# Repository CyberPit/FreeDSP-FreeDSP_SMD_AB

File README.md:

# FreeDSP-FreeDSP_SMD_AB

- 2in4out RCA jacks
- A/B Selectable Boot EEPROMs
- ADAU1701 Single Board solution
- 0805(2.0mm x 1.25mm) SMD Resistors
- Through-hole Ele-Caps for better Audio performance
- 2V RMS Unity Gain Analog Audio I/O
- Absolute Phase Transparent.
- Power ON/OFF Audio Pops-Muting
- Buffered I2S I/O Headers (with Output Enable control feature)
- Onboard three semi-potentiometers or external controls via header pin. 

Project web page: (Direct Link)
https://cyberpithilo.web.fc2.com/audio/freedsp/index.html

Project web page: (Yandex Machine Translation)
https://translate.yandex.com/translate?url=https%3A%2F%2Fcyberpithilo.web.fc2.com%2Faudio%2Ffreedsp%2Findex.html&lang=ja-en

Project web page: (Google Machine Translation)
https://translate.google.com/translate?hl=ja&sl=ja&tl=en&u=https%3A%2F%2Fcyberpithilo.web.fc2.com%2Faudio%2Ffreedsp%2Findex.html

I registered this design at SeedStudio(FusionPCB) project Gallary, so you can order this board here easily https://www.seeedstudio.com/FreeDSP-SMD-A-B-ADAU1701-1401-Audio-DSP-Processing-Boar-g-1230721

# License
This work and all other materials under https://github.com/freeDSP are licensed under a Creative Commons Attribution Share-Alike 4.0 license. This allows for both personal and commercial derivative works, as long as they credit freeDSP and release their designs under the same license.

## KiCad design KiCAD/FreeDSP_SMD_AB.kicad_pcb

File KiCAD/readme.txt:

This PCB design was inherit from FreeDSP SMD.
Canages and improved in many points.
- Unity Gain I/O
- Selectable boot EEPROM
- Power ON/OFF Mute
- Buffered I2S I/O Headers

Errata: R49 47k ohms --> 4.7k ohms (Need to pull-up strong)

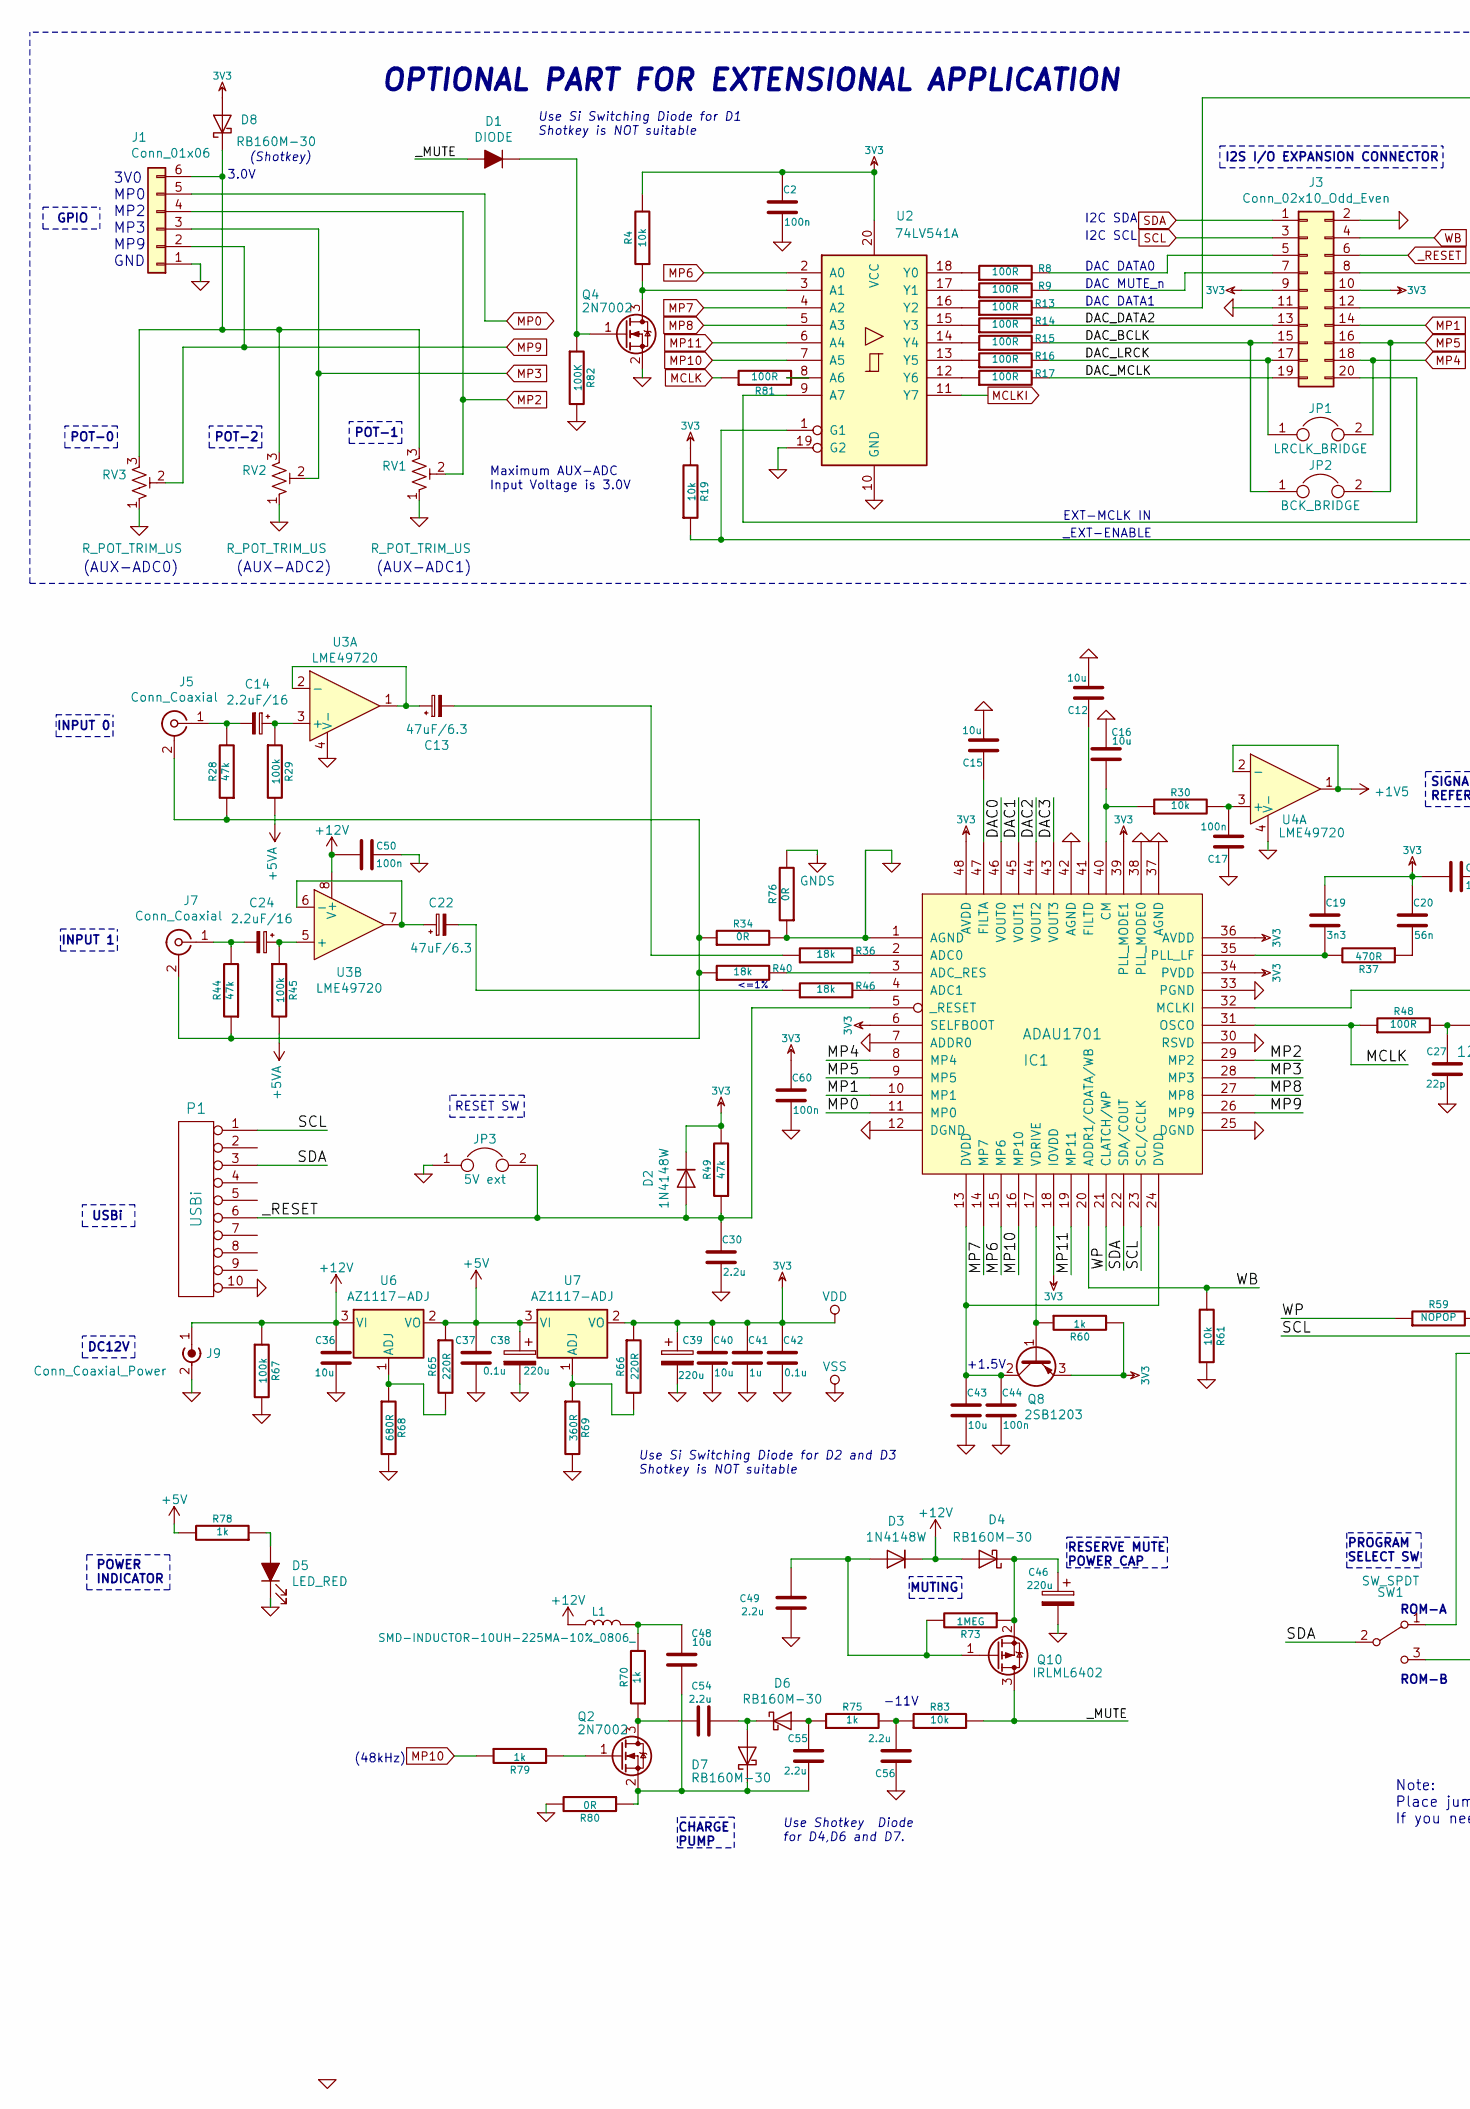
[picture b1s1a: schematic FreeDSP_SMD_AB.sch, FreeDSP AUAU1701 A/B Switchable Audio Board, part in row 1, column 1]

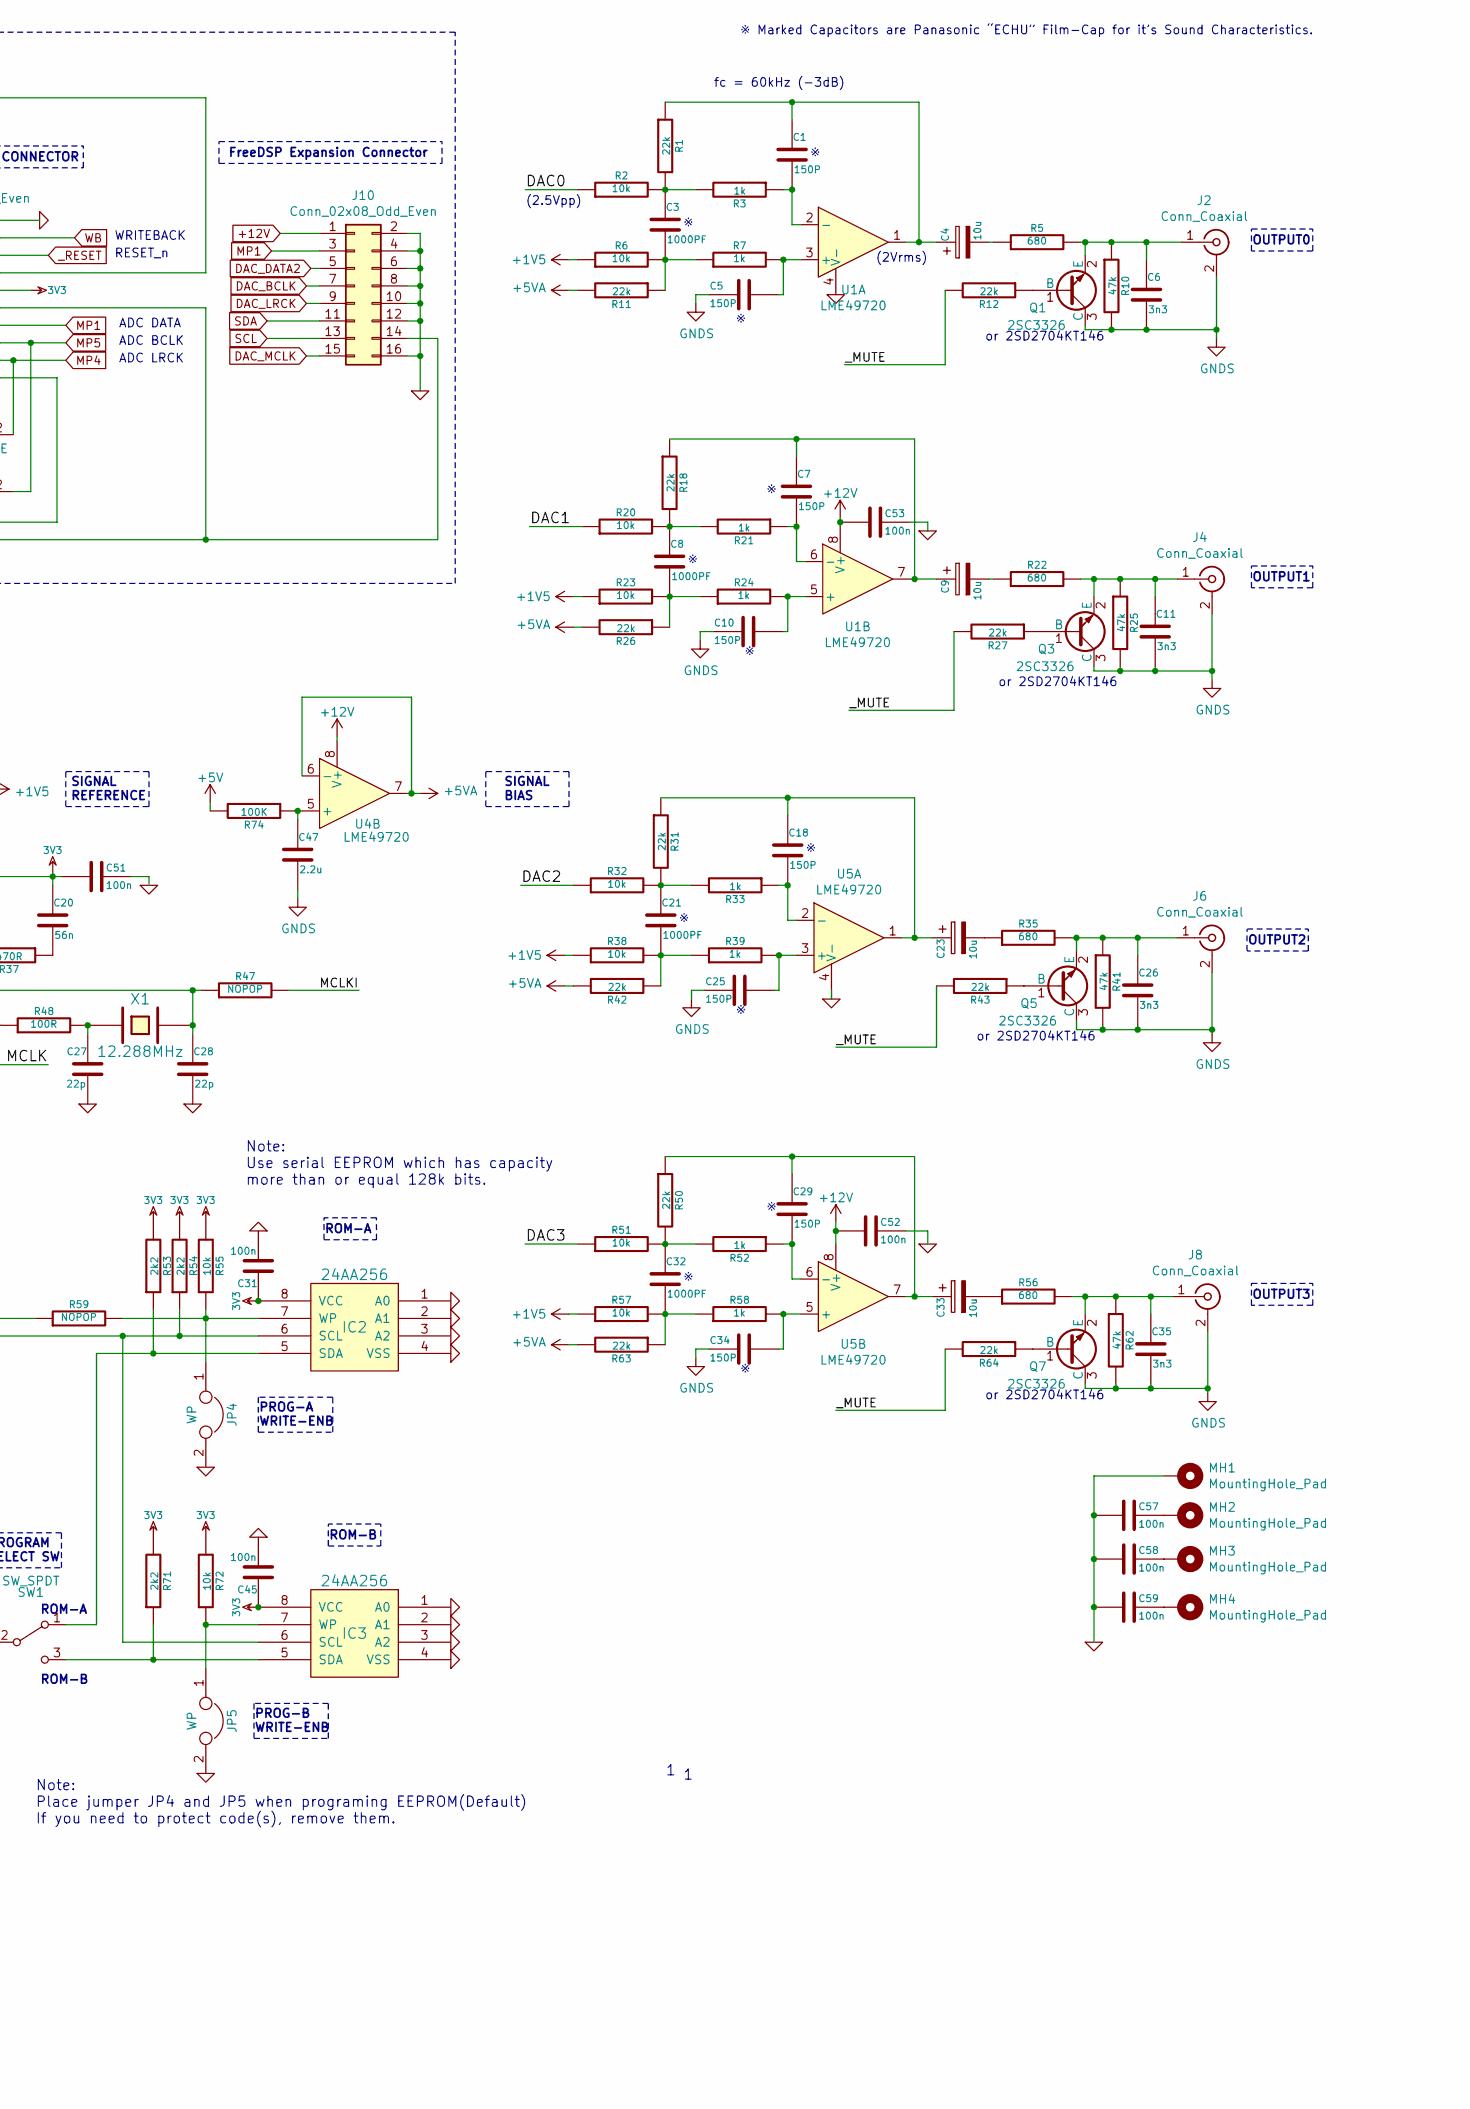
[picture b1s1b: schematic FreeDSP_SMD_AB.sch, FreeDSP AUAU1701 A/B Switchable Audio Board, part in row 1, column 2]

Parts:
C1, C5, C7, C10, C18, C25, C29, C34: 150P; C_0805_HandSoldering
C2, C17, C31, C44, C45, C50, C51, C52, C53, C57, C58, C59, C60: 100n; C_0805_HandSoldering
C3, C8, C21, C32: 1000PF; C_0805_HandSoldering
C4, C9, C23, C33: 10u; CP_Radial_D5.0mm_P2.00mm
C6, C11, C19, C26, C35: 3n3; C_0805_HandSoldering
C12, C15, C16, C36, C40, C43: 10u; C_0805_HandSoldering
C13, C22: 47uF/6.3; CP_Radial_D4.0mm_P2.00mm
C14, C24: 2.2uF/16; CP_Radial_D4.0mm_P2.00mm
C20: 56n; C_0805_HandSoldering
C27, C28: 22p; C_0805_HandSoldering
C30, C47, C49, C54, C55, C56: 2.2u; C_0805_HandSoldering
C37, C42: 0.1u; C_0805_HandSoldering
C38, C39: 220u; CP_Radial_D8.0mm_P5.00mm
C41: 1u; C_0805_HandSoldering
C46: 220u; CP_Radial_Tantal_D10.5mm_P5.00mm
C48: 10u; C_1206_HandSoldering
D1: DIODE; D_SOD-123
D2, D3: 1N4148W; D_SOD-123
D4, D6, D7, D8: RB160M-30; D_SOD-123
D5: LED_RED; LED_0603_HandSoldering
IC1: ADAU1701; LQFP-48_7x7mm_Pitch0.5mm
IC2, IC3: 24AA256; SOIC-8_3.9x4.9mm_Pitch1.27mm
J1: Conn_01x06; TerminalBlock_Phoenix_MPT-2.54mm_6pol
J2, J4, J5, J6, J7, J8: Conn_Coaxial; RJ-2410N
J3: Conn_02x10_Odd_Even; Multicomp_MC9A12-2034_2x10x2.54mm_Straight
J9: Conn_Coaxial_Power; BARREL_JACK
J10: Conn_02x08_Odd_Even; Pin_Header_Straight_2x08_Pitch2.54mm
JP1: LRCLK_BRIDGE; Pin_Header_Straight_1x02_Pitch2.54mm
JP2: BCK_BRIDGE; Pin_Header_Straight_1x02_Pitch2.54mm
JP3: 5V ext; Pin_Header_Straight_1x02_Pitch2.54mm
JP4, JP5: WP; Pin_Header_Straight_1x02_Pitch2.54mm
L1: SMD-INDUCTOR-10UH-225MA-10%_0806_; Inductor_1212; MPN LQH2MCN100K02L
MH1: MountingHole_Pad; MountingHole_3.2mm_M3_Pad_Via
MH2, MH3, MH4: MountingHole_Pad; MountingHole_3.2mm_M3_Pad
P1: USBi; Multicomp_MC9A12-1034_2x05x2.54mm_Straight
Q1, Q3, Q5, Q7: 2SC3326; SOT-23
Q2, Q4: 2N7002; SOT-23
Q8: 2SB1203; TO-252-2
Q10: IRLML6402; SOT-23
R1, R11, R12, R18, R26, R27, R31, R42, R43, R50, R63, R64: 22k; R_0805_HandSoldering
R2, R4, R6, R19, R20, R23, R30, R32, R38, R51, R55, R57, R61, R72, R83: 10k; R_0805_HandSoldering
R3, R7, R21, R24, R33, R39, R52, R58, R60, R70, R75, R78, R79: 1k; R_0805_HandSoldering
R5, R22, R35, R56: 680; R_0805_HandSoldering
R8, R9, R13, R14, R15, R16, R17, R48, R81: 100R; R_0805_HandSoldering
R10, R25, R28, R41, R44, R49, R62: 47k; R_0805_HandSoldering
R29, R45, R67: 100k; R_0805_HandSoldering
R34, R76, R80: 0R; R_0805_HandSoldering
R36, R40, R46: 18k; R_0805_HandSoldering
R37: 470R; R_0805_HandSoldering
R47, R59: NOPOP; R_0805_HandSoldering
R53, R54, R71: 2k2; R_0805_HandSoldering
R65, R66: 220R; R_0805_HandSoldering
R68: 680R; R_0805_HandSoldering
R69: 360R; R_0805_HandSoldering
R73: 1MEG; R_0805_HandSoldering
R74, R82: 100K; R_0805_HandSoldering
RV1, RV2, RV3: R_POT_TRIM_US; Potentiometer_Trimmer_Bourns_3339P_Horizontal
SW1: SW_SPDT; Switch_Slide_11.6x4mm_EG1218
U1, U3, U4, U5: LME49720; SOIC127P600X175-8N
U2: 74LV541A; TSSOP-20_W4.4mm
U6, U7: AZ1117-ADJ; SOT-223-3_TabPin2
X1: 12.288MHz; Crystal_HC49-U_Vertical

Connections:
3V3: C2.1, C19.1, C20.1, C31.1, C39.1, C40.1, C41.1, C42.1, C45.1, C51.2, C60.1, D2.1 (K), D8.2 (A), IC1.6 (SELFBOOT), IC1.18 (IOVDD), IC1.34 (PVDD), IC1.36 (AVDD), IC1.39 (PLL_MODE1), IC1.48 (AVDD), IC2.8 (VCC), IC3.8 (VCC), J3.9, J3.10, Q8.3 (E), R4.2, R19.2, R49.2, R53.2, R54.2, R55.2, R60.2, R66.1, R71.2, R72.2, U2.20 (VCC), U7.2 (VO)
+1V5: R6.1, R23.1, R38.1, R57.1, U4.1, U4.2 (-)
+5V: C37.1, C38.1, R65.1, R74.2, R78.2, U6.2 (VO), U7.3 (VI)
+5VA: R11.2, R26.2, R29.2, R42.2, R45.2, R63.2, U4.6 (-), U4.7
+12V: C36.1, C50.2, C52.2, C53.2, D3.1 (K), D4.2 (A), J9.1 (In), J10.1, L1.1, R67.1, U1.8 (V+), U3.8 (V+), U4.8 (V+), U5.8 (V+), U6.3 (VI)
/DAC0: IC1.46 (VOUT0), R2.1
/DAC1: IC1.45 (VOUT1), R20.1
/DAC2: IC1.44 (VOUT2), R32.1
/DAC3: IC1.43 (VOUT3), R51.1
/WP: IC1.21 (CLATCH/WP), R59.1
/_MUTE: D1.2 (A), Q10.3 (D), R12.2, R27.2, R43.2, R64.2, R83.2
DAC_BCLK: J3.15, J10.7, JP2.1, R15.2
DAC_DATA2: J3.13, J10.5, R14.2
DAC_LRCK: J3.17, J10.9, JP1.1, R16.2
DAC_MCLK: J3.19, J10.15, R17.2
GND: C2.2, C12.2, C15.2, C16.2, C17.1, C27.2, C28.2, C30.2, C31.2, C36.2, C37.2, C38.2, C39.2, C40.2, C41.2, C42.2, C43.2, C44.2, C45.2, C46.2, C49.2, C50.1, C51.1, C52.1, C53.1, C56.1, C57.2, C58.2, C59.2, C60.2, D5.1 (K), IC1.1 (AGND), IC1.7 (ADDR0), IC1.12 (DGND), IC1.25 (DGND), IC1.30 (RSVD), IC1.33 (PGND), IC1.37 (AGND), IC1.38 (PLL_MODE0), IC1.42 (AGND), IC2.1 (A0), IC2.2 (A1), IC2.3 (A2), IC2.4 (VSS), IC3.1 (A0), IC3.2 (A1), IC3.3 (A2), IC3.4 (VSS), J1.1, J3.2, J3.11, J9.2 (Ext), J10.2, J10.4, J10.6, J10.8, J10.10, J10.12, J10.16, JP3.1, JP4.2, JP5.2, MH1.1, P1.10, Q4.2 (S), R34.2, R61.1, R67.2, R68.2, R69.2, R76.1, R80.2, R82.2, RV1.1, RV2.1, RV3.1, U1.4 (V-), U2.10 (GND), U2.19 (G2), U3.4 (V-), U4.4 (V-), U5.4 (V-)
GNDS: C5.2, C6.2, C10.2, C11.2, C25.2, C26.2, C34.2, C35.2, C47.2, J2.2 (Ext), J4.2 (Ext), J6.2 (Ext), J8.2 (Ext), Q1.3 (C), Q3.3 (C), Q5.3 (C), Q7.3 (C), R10.2, R25.2, R41.2, R62.2, R76.2
MCLK: IC1.31 (OSCO), R48.1, R81.1
MCLKI: R47.2, U2.11 (Y7)
MP0: IC1.11 (MP0), J1.5
MP1: IC1.10 (MP1), J3.14, J10.3
MP2: IC1.29 (MP2), J1.4, RV1.2
MP3: IC1.28 (MP3), J1.3, RV2.2
MP4: IC1.8 (MP4), J3.18, JP1.2
MP5: IC1.9 (MP5), J3.16, JP2.2
MP6: IC1.15 (MP6), U2.2 (A0)
MP7: IC1.14 (MP7), U2.4 (A2)
MP8: IC1.27 (MP8), U2.5 (A3)
MP9: IC1.26 (MP9), J1.2, RV3.2
MP10: IC1.16 (MP10), R79.1, U2.7 (A5)
MP11: IC1.19 (MP11), U2.6 (A4)
unnamed: C1.1, C4.1, R1.1, U1.1
unnamed: C1.2, R3.1, U1.2 (-)
unnamed: C3.1, R1.2, R2.2, R3.2
unnamed: C3.2, R6.2, R7.1, R11.1
unnamed: C4.2, R5.1
unnamed: C5.1, R7.2, U1.3 (+)
unnamed: C6.1, J2.1 (In), Q1.2 (E), R5.2, R10.1
unnamed: C7.1, C9.1, R18.1, U1.7
unnamed: C7.2, R21.1, U1.6 (-)
unnamed: C8.1, R18.2, R20.2, R21.2
unnamed: C8.2, R23.2, R24.1, R26.1
unnamed: C9.2, R22.1
unnamed: C10.1, R24.2, U1.5 (+)
unnamed: C11.1, J4.1 (In), Q3.2 (E), R22.2, R25.1
unnamed: C12.1, IC1.41 (FILTD)
unnamed: C13.1, U3.1, U3.2 (-)
unnamed: C13.2, R36.1
unnamed: C14.1, R29.1, U3.3 (+)
unnamed: C14.2, J5.1 (In), R28.2
unnamed: C15.1, IC1.47 (FILTA)
unnamed: C16.1, IC1.40 (CM), R30.1
unnamed: C17.2, R30.2, U4.3 (+)
unnamed: C18.1, C23.1, R31.1, U5.1
unnamed: C18.2, R33.1, U5.2 (-)
unnamed: C19.2, IC1.35 (PLL_LF), R37.2
unnamed: C20.2, R37.1
unnamed: C21.1, R31.2, R32.2, R33.2
unnamed: C21.2, R38.2, R39.1, R42.1
unnamed: C22.1, U3.6 (-), U3.7
unnamed: C22.2, R46.1
unnamed: C23.2, R35.1
unnamed: C24.1, R45.1, U3.5 (+)
unnamed: C24.2, J7.1 (In), R44.2
unnamed: C25.1, R39.2, U5.3 (+)
unnamed: C26.1, J6.1 (In), Q5.2 (E), R35.2, R41.1
unnamed: C27.1, R48.2, X1.1
unnamed: C28.1, IC1.32 (MCLKI), R47.1, X1.2
unnamed: C29.1, C33.1, R50.1, U5.7
unnamed: C29.2, R52.1, U5.6 (-)
unnamed: C32.1, R50.2, R51.2, R52.2
unnamed: C32.2, R57.2, R58.1, R63.1
unnamed: C33.2, R56.1
unnamed: C34.1, R58.2, U5.5 (+)
unnamed: C35.1, J8.1 (In), Q7.2 (E), R56.2, R62.1
unnamed: C43.1, C44.1, IC1.13 (DVDD), IC1.24 (DVDD), Q8.2 (C)
unnamed: C46.1, D4.1 (K), Q10.2 (S), R73.1
unnamed: C47.1, R74.1, U4.5 (+)
unnamed: C48.1, L1.2, R70.2
unnamed: C48.2, C55.2, D7.1 (K), Q2.2 (S), R80.1
unnamed: C49.1, D3.2 (A), Q10.1 (G), R73.2
unnamed: C54.1, Q2.3 (D), R70.1
unnamed: C54.2, D6.1 (K), D7.2 (A)
unnamed: C55.1, D6.2 (A), R75.1
unnamed: C56.2, R75.2, R83.1
unnamed: C57.1, MH2.1
unnamed: C58.1, MH3.1
unnamed: C59.1, MH4.1
unnamed: D1.1 (K), Q4.1 (G), R82.1
unnamed: D5.2 (A), R78.1
unnamed: D8.1 (K), J1.6, RV1.3, RV2.3, RV3.3
unnamed: IC1.2 (ADC0), R36.2
unnamed: IC1.3 (ADC_RES), R40.2
unnamed: IC1.4 (ADC1), R46.2
unnamed: IC1.17 (VDRIVE), Q8.1 (B), R60.1
unnamed: IC2.5 (SDA), R53.1, SW1.1 (A)
unnamed: IC2.7 (WP), JP4.1, R55.1, R59.2
unnamed: IC3.5 (SDA), R71.1, SW1.3 (C)
unnamed: IC3.7 (WP), JP5.1, R72.1
unnamed: J3.5, R8.2
unnamed: J3.7, R9.2
unnamed: J3.8, R13.2
unnamed: J3.20, U2.9 (A7)
unnamed: J5.2 (Ext), J7.2 (Ext), R28.1, R34.1, R40.1, R44.1
unnamed: J3.12, J10.14, R19.1, U2.1 (G1)
unnamed: Q1.1 (B), R12.1
unnamed: Q2.1 (G), R79.2
unnamed: Q3.1 (B), R27.1
unnamed: Q4.3 (D), R4.1, U2.3 (A1)
unnamed: Q5.1 (B), R43.1
unnamed: Q7.1 (B), R64.1
unnamed: R8.1, U2.18 (Y0)
unnamed: R9.1, U2.17 (Y1)
unnamed: R13.1, U2.16 (Y2)
unnamed: R14.1, U2.15 (Y3)
unnamed: R15.1, U2.14 (Y4)
unnamed: R16.1, U2.13 (Y5)
unnamed: R17.1, U2.12 (Y6)
unnamed: R65.2, R68.1, U6.1 (ADJ)
unnamed: R66.2, R69.1, U7.1 (ADJ)
unnamed: R81.2, U2.8 (A6)
SCL: IC1.23 (SCL/CCLK), IC2.6 (SCL), IC3.6 (SCL), J3.3, J10.13, P1.1, R54.1
SDA: IC1.22 (SDA/COUT), J3.1, J10.11, P1.3, SW1.2 (B)
WB: IC1.20 (ADDR1/CDATA/WB), J3.4, R61.2
_RESET: C30.1, D2.2 (A), IC1.5 (_RESET), J3.6, JP3.2, P1.6, R49.1

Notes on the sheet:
<=1%
RESET SW
DAC DATA0
DAC MUTE_n
I2C SCL
I2C SDA
RESET_n
DAC DATA1
EXT-MCLK IN
ADC LRCK
ADC BCLK
ADC DATA
I2S I/O EXPANSION CONNECTOR
WRITEBACK
POT-0
POT-1
POT-2
ROM-A
ROM-B
USBi
DC12V
fc = 60kHz (-3dB)
(2.5Vpp)
(2Vrms)
MUTING
INPUT 0
INPUT 1
OUTPUT0
OUTPUT1
OUTPUT2
OUTPUT3
PROGRAM SELECT SW
SIGNAL REFERENCE
SIGNAL BIAS
_EXT-ENABLE
PROG-A WRITE-ENB
PROG-B WRITE-ENB
GPIO
3V0 MP0 MP2 MP3 MP9 GND
OPTIONAL PART FOR EXTENSIONAL APPLICATION

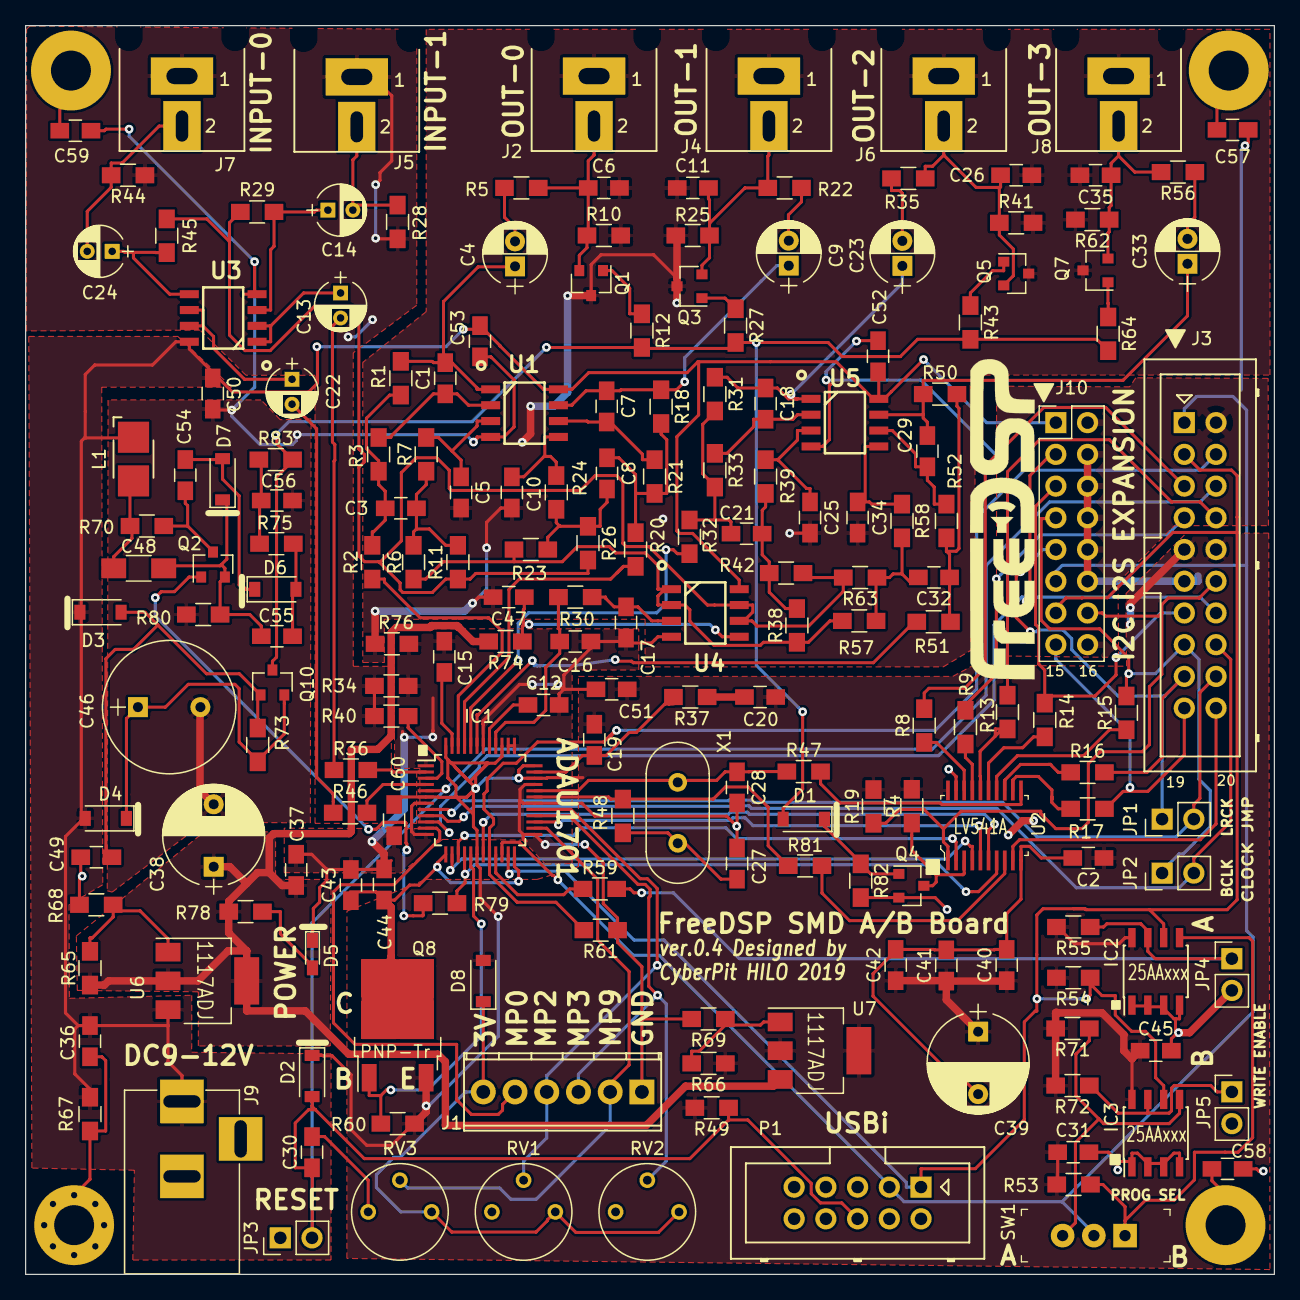
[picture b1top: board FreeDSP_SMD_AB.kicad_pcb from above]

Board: 2 copper layers, 100.0 x 100.0 mm, 194 parts (0 on the bottom side), 125 nets.

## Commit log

2019-08-10 version 0.4 FreeDSP SMD A/B Board Top View
2019-08-10 Parallel connected, Just pass through to all OUT
2019-08-10 Parallel connected, Just pass through.
2019-08-10 Measured overall frequency response.
2019-08-10 Actual Audio performance (ADC -> DSP -> DAC)
2020-11-21 Fixed R49 value to 4.7k
